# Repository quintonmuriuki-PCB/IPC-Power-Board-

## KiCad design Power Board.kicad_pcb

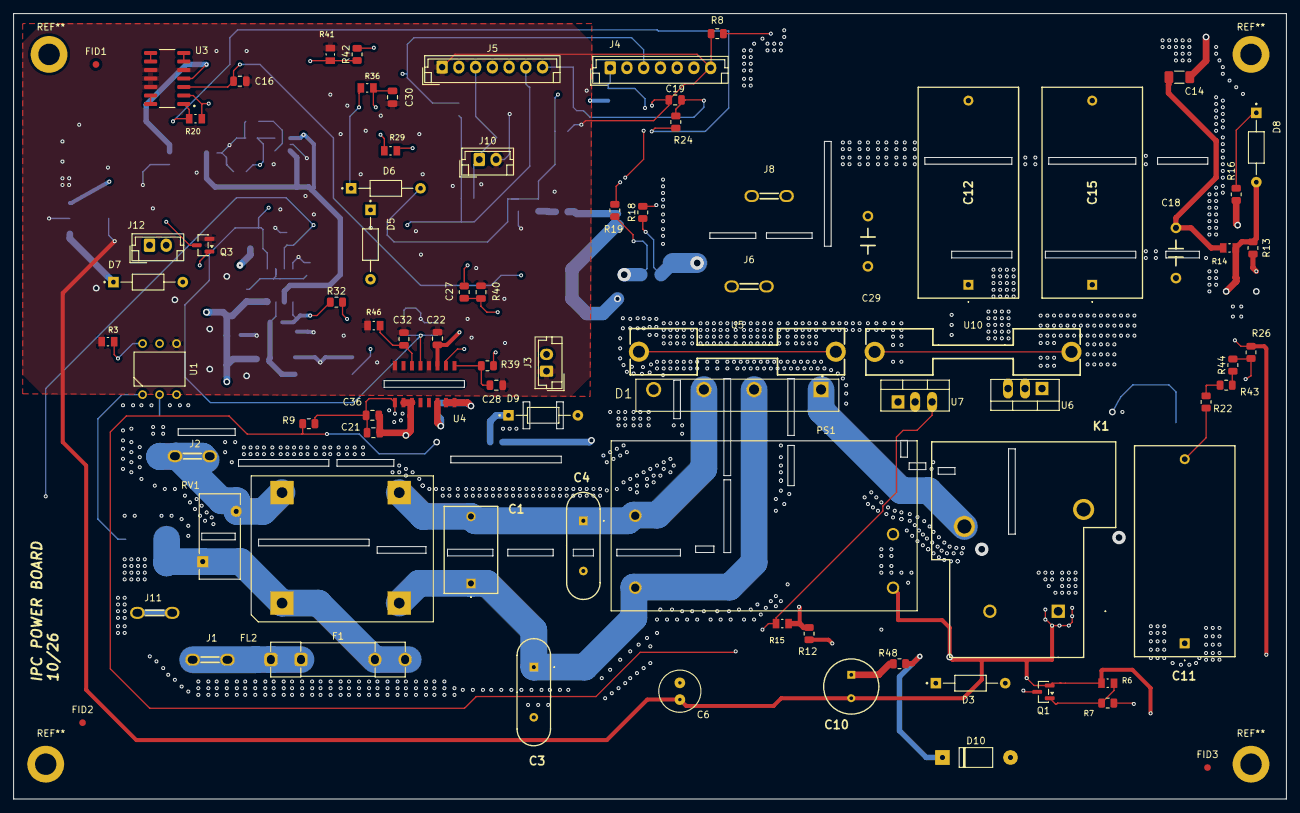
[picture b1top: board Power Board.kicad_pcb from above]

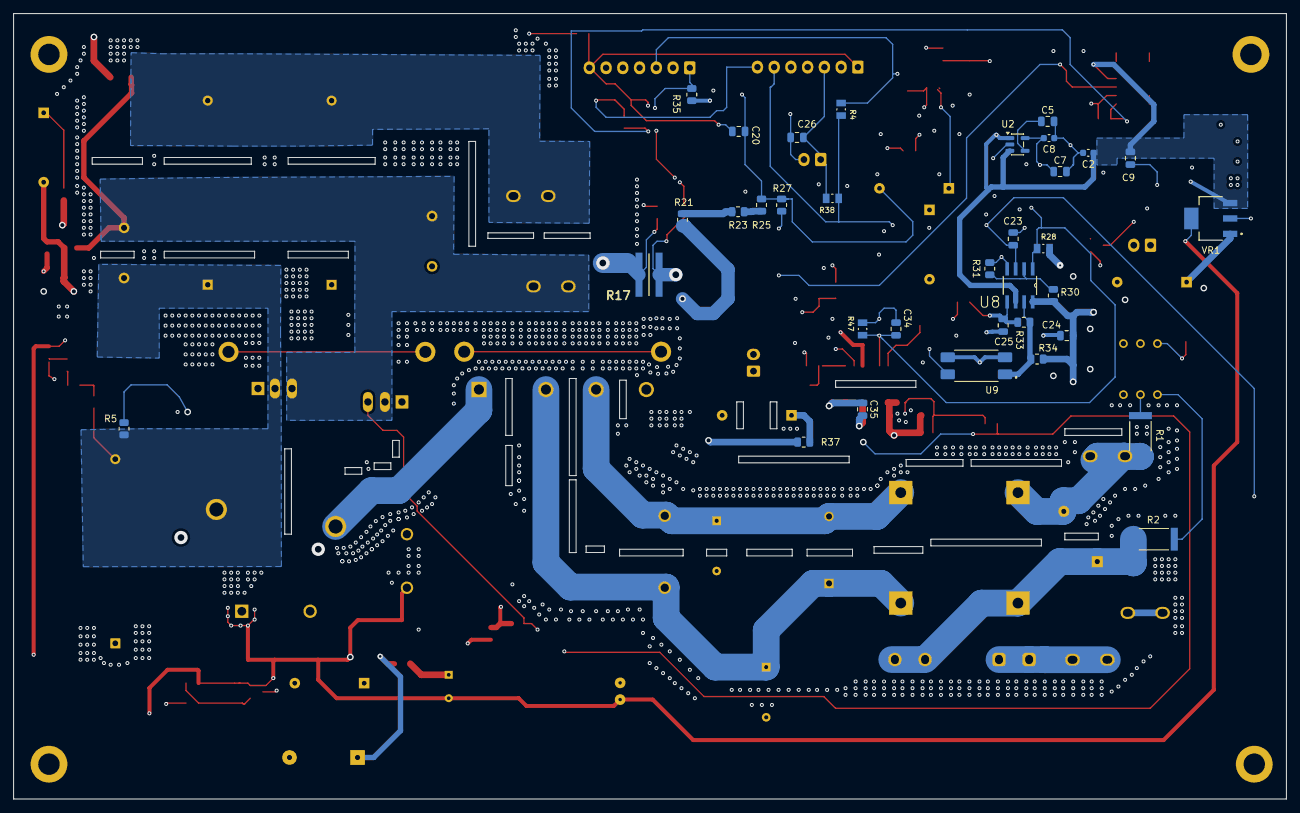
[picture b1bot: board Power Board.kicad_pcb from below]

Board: 4 copper layers, 190.1 x 117.3 mm, 116 parts (34 on the bottom side), 58 nets.

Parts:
C1: 0.22uF; 890334023028CS
C2, C8: 10uF; C_0603_1608Metric
C3, C4: 2.2nF; VY2103M63Y5UG63V7
C5: 470pF; C_0805_2012Metric
C6: 0.22uf; C_Radial_D10.0mm_H16.0mm_P5.00mm
C7: 2.2uF; C_0805_2012Metric
C9: 0.1uf; C_0805_2012Metric
C10: 470uF; CAPPRD350W60D825H1150
C11: 10uF; B32774D4106K000
C12, C15: 0.47uF; B32774D4106K000
C14: 1uF; C_1206_3216Metric_Pad1.33x1.80mm_HandSolder
C16, C19, C20: 1nF; C_0805_2012Metric
C18, C29: 1nF; CAP-TH_L11.0-W5.5-P7.50-D0.6
C21: 1uF; C_0805_2012Metric
C22, C35, C36: 0.1uF; C_0805_2012Metric
C23, C25, C32: 2.2nF; C_0805_2012Metric
C24: 100nF; C_0805_2012Metric
C26, C30: 4.7uF; C_0805_2012Metric
C27, C28: 33pF; C_0805_2012Metric
C34: 0.01uF; C_0805_2012Metric
D1: GBJ2510; DIOB_GBJ2510
D3, D7: 1N5819; DIOAD1036W78L470D235
D5, D6, D8, D9: D_Schottky; DIOAD1036W78L470D235
D10: MUR160; P1_DO-41
F1: 15AMP; Fuseholder_Clip-5x20mm_Littelfuse_519_Inline_P20.60x5.00mm_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
FID1, FID2, FID3: Fiducial; Fiducial_1mm_Mask2mm
FL2: 2.5mH; L_CommonMode_PulseElectronics_PH9455x705NL_1
J1: L; TH-2_L6.0-W0.8_C5454586
J2: N; TH-2_L6.0-W0.8_C5454586
J3: Conn_01x02; JST_EH_B2B-EH-A_1x02_P2.50mm_Vertical
J4, J5: Conn_01x07; JST_EH_B7B-EH-A_1x07_P2.50mm_Vertical
J6: coil1_+; TH-2_L6.0-W0.8_C5454586
J8: coil1_-; TH-2_L6.0-W0.8_C5454586
J10: POT TEMP; JST_EH_B2B-EH-A_1x02_P2.50mm_Vertical
J11: E; TH-2_L6.0-W0.8_C5454586
J12: FAN; JST_EH_B2B-EH-A_1x02_P2.50mm_Vertical
K1: 832A-1A-F-C-B-12VDC; 832A1AFCB12VDC
PS1: IRM-10-12; CONV_IRM-10-12
Q1, Q3: AO3400A; SOT-23
R1, R2: 47k; RESC6332X65N
R3: 200k; RESC2012X65N
R4, R6, R14, R15, R47: 10k; RESC2012X65N
R5, R12, R13, R16, R37, R42, R48: 10R; R_0805_2012Metric
R7: 100R; R_0805_2012Metric
R8, R9: 0R; R_0805_2012Metric
R17: 10m; RESC3264X70N
R18, R19, R34: 1k; R_0805_2012Metric
R20: 15k; RESC2012X65N
R21, R22, R23, R25, R43, R44: 330k; R_0805_2012Metric
R24, R27, R31, R32, R35: 10k; R_0805_2012Metric
R26: 13k; R_0805_2012Metric
R28: 6.8k; RESC2012X65N
R29: 470k; RESC2012X65N
R30: 20k; R_0805_2012Metric
R33: 470k; R_0805_2012Metric
R36: 2.2k; RESC2012X65N
R38: 2.5k; RESC2012X65N
R39, R40: 51R; R_0805_2012Metric
R41: 4.3k; RESC2012X65N
R46: 20k; RESC2012X65N
RV1: 275 VAC; MOV-10D561K_BRN
U1: H11AA1M; DIP6
U2: MIC5219-3.3YM5; SOT-23-5
U3: LM2902; SOIC127P600X175-14N
U4: UCC21222DR; D0016B
U5, U10: 32*7*20 2个钉散热板; HEATSINK-TH_L32.0-W6.9-P29.4
U6, U7: GT50JR22(S1WLD,E,S; TO-220-3_Vertical
U8: LM393D; SOIC127P600X175-8N
U9: PC817X2NIP1B; SOIC254P960X420-4N
VR1: LM7805MPX_NOPB; VREG_LM7805MPX_NOPB

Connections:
+3.3V: C7.1, C8.1, D5.C, D6.C, J5.6, R4.2, R36.1, R38.1, U2.5 (OUT)
+5V: C2.1, C9.1, C22.1, R35.2, U2.1 (IN), U2.3 (EN), U3.4 (V+), U4.3 (VCCI), U8.6 (2IN-), VR1.3 (OUTPUT)
+12V: C6.1, C10.1, C21.1, C24.1, C36.1, D3.C, D7.C, J12.1, K1.1 (COIL_1), PS1.+V, R12.2, R28.2, R30.2, R34.2, R37.1, R48.1, U4.10 (OUTB), U4.11 (VDDB), U8.8 (VCC), VR1.1 (INPUT)
/AC_Live: F1.1, J1.1, J1.2
/AC_Live_: C1.1, C3.1, D1.2, FL2.2, PS1.AC_L (AC/L)
/AC_Neut: FL2.4, J2.1, J2.2, R1.2, RV1.2
/induction coil driver/coil_+: C14.2, C18.2, C29.1, C35.2, J6.1, J6.2, R14.2, R21.1, U4.14 (VSSA), U6.3 (E), U7.2 (C)
/induction coil driver/coil_-: C12.2, C15.2, J8.1, J8.2
CURRENT SENSE: C19.2, D5.A, J5.7, R24.2
DIS: C34.1, J5.4, R28.1, R29.1, R47.1, U4.5 (DISABLE), U8.1 (1OUT)
Earth: C3.2, C4.2, J11.1, J11.2, U5.1, U5.2, U10.1, U10.2
FAN: J5.5, R42.2
GND: C2.2, C5.2, C6.2, C7.2, C8.2, C9.2, C10.2, C16.1, C19.1, C20.2, C22.2, C23.2, C24.2, C25.1, C26.2, C27.2, C28.2, C30.2, C32.2, C34.2, J3.1, J4.7, J5.1, J10.2, PS1.-V, Q1.2 (S), Q3.2 (S), R3.1, R6.1, R8.2, R27.1, R31.2, R41.2, R46.2, R47.2, U1.P$4 (E), U2.2 (GND), U3.5 (+), U3.10 (+), U3.11 (V-), U3.12 (+), U4.4 (GND), U4.8 (VCCI), U8.4 (GND), U9.2, U9.3, VR1.2 (GND_2), VR1.4 (GND_4)
GNDPWR: C11.1, D1.4, R8.1, R9.2, R17.2, R19.2, R26.2
IGBT_IN_A: J4.5, R39.1
IGBT_IN_B: J4.6, R40.1
NTC: C30.1, J3.2, J5.2, R36.2
unnamed: D8.C, R16.2
unnamed: D9.C, R37.2
unnamed: D10.1 (A), R48.2
unnamed: C14.1, C35.1, D10.2 (K), R13.1, R16.1, U4.15 (OUTA), U4.16 (VDDA)
unnamed: F1.2, FL2.1, R2.1, RV1.1
unnamed: D7.A, J12.2, Q3.3 (D)
unnamed: D3.A, K1.2 (COIL_2), Q1.3 (D)
unnamed: D1.1, K1.4 (COM), R5.1
unnamed: C1.2, C4.1, D1.3, FL2.3, PS1.AC_N (AC/N)
unnamed: Q1.1 (G), R6.2, R7.1
unnamed: Q3.1 (G), R41.1, R42.1
unnamed: R20.2, R24.1, U3.1
unnamed: R21.2, R23.1
unnamed: R22.2, R43.1
unnamed: R23.2, R25.1
unnamed: R43.2, R44.1
unnamed: R3.2, U1.P$6 (B)
unnamed: R2.2, U1.P$1 (IN1)
unnamed: R1.1, U1.P$2 (IN2)
unnamed: C5.1, U2.4 (BP)
unnamed: C16.2, R18.2, U3.3 (+)
unnamed: R19.1, R20.1, U3.2 (-)
unnamed: U3.6 (-), U3.7
unnamed: U3.8, U3.9 (-)
unnamed: U3.13 (-), U3.14
unnamed: C32.1, R46.1, U4.6 (DT)
unnamed: C28.1, R39.2, U4.1 (INA)
unnamed: C27.1, R40.2, U4.2 (INB)
unnamed: D8.A, R13.2, R14.1, U6.1 (G)
unnamed: D9.A, R12.1, R15.1, U7.1 (G)
unnamed: C23.1, R26.1, R29.2, R32.2, R44.2, U8.3 (1IN+)
unnamed: R30.1, R31.1, U8.2 (1IN-)
unnamed: C25.2, R32.1, R33.1, U8.5 (2IN+)
unnamed: R33.2, R34.1, U8.7 (2OUT), U9.1
OVP: J4.1, R35.1, U9.4
POT TEMP: C26.1, J5.3, J10.1, R38.2
Pulse_Det.: C20.1, D6.A, J4.4, R25.2, R27.2
Relay: J4.2, R7.2
VSSB: C12.1, C21.2, C29.2, C36.2, R9.1, R15.2, R17.1, R18.1, U4.9 (VSSB), U7.3 (E)
ZCD_OUT: J4.3, R4.1, U1.P$5 (C)
coil+340V: C11.2, C15.1, C18.1, K1.5 (NO), R5.2, R22.1, U6.2 (C)
